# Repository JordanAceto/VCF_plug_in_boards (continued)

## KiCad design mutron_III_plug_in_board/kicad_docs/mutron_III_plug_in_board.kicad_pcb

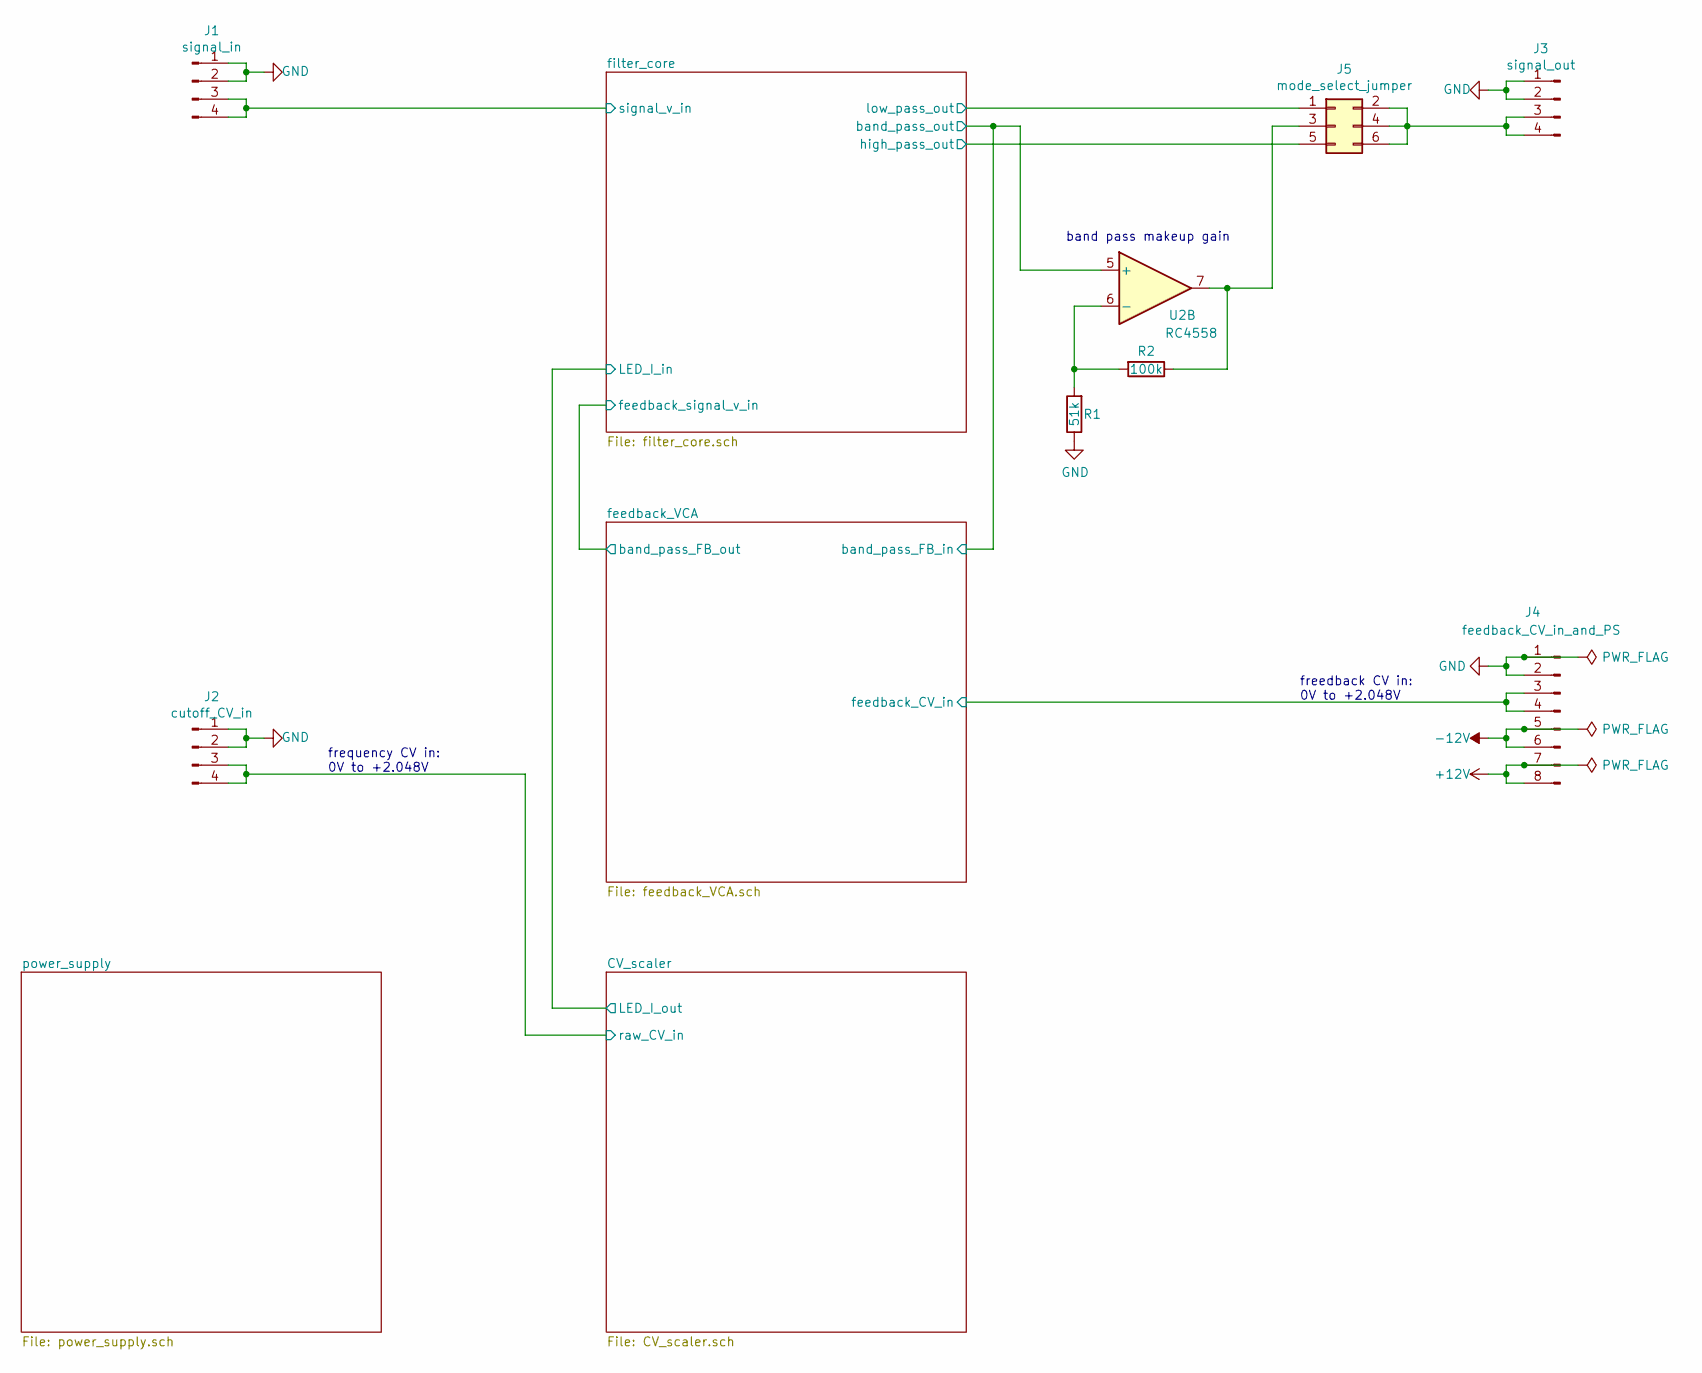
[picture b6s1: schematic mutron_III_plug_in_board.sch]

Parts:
J1: signal_in; PinHeader_1x04_P2.54mm_Vertical
J2: cutoff_CV_in; PinHeader_1x04_P2.54mm_Vertical
J3: signal_out; PinHeader_1x04_P2.54mm_Vertical
J4: feedback_CV_in_and_PS; PinHeader_1x08_P2.54mm_Vertical
J5: mode_select_jumper; PinHeader_2x03_P2.54mm_Vertical
R1: 51k; R_0805_2012Metric_Pad1.15x1.40mm_HandSolder
R2: 100k; R_0805_2012Metric_Pad1.15x1.40mm_HandSolder
U2: RC4558; SOIC-8_3.9x4.9mm_P1.27mm

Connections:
+12V: J4.7, J4.8; also elsewhere on the board
-12V: J4.5, J4.6; also elsewhere on the board
/CV_scaler/raw_CV_in: J2.3, J2.4; also elsewhere on the board
/feedback_VCA/band_pass_FB_in: U2.5 (+); also elsewhere on the board
/feedback_VCA/feedback_CV_in: J4.3, J4.4; also elsewhere on the board
/filter_core/high_pass_out: J5.5; also elsewhere on the board
/filter_core/low_pass_out: J5.1; also elsewhere on the board
/filter_core/signal_v_in: J1.3, J1.4; also elsewhere on the board
GND: J1.1, J1.2, J2.1, J2.2, J3.1, J3.2, J4.1, J4.2, R1.1; also elsewhere on the board
unnamed: J3.3, J3.4, J5.2, J5.4, J5.6
unnamed: J5.3, R2.1, U2.7
unnamed: R1.2, R2.2, U2.6 (-)

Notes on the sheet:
frequency CV in: 0V to +2.048V
freedback CV in: 0V to +2.048V
band pass makeup gain

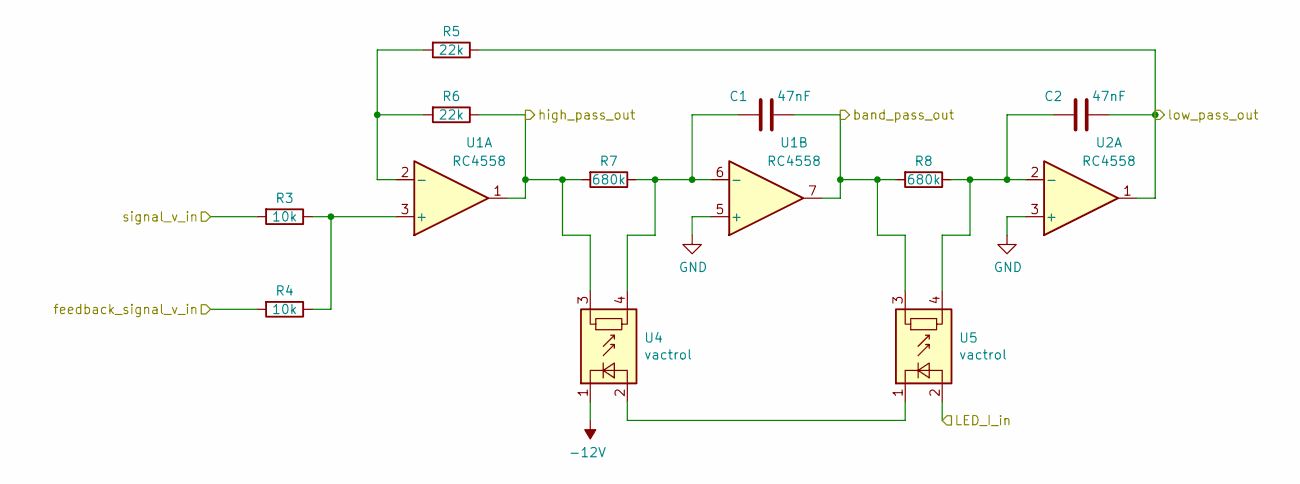
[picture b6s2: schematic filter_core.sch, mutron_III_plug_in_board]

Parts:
C1, C2: 47nF; C_Rect_L7.0mm_W3.5mm_P5.00mm
R3, R4: 10k; R_0805_2012Metric_Pad1.15x1.40mm_HandSolder
R5, R6: 22k; R_0805_2012Metric_Pad1.15x1.40mm_HandSolder
R7, R8: 680k; R_0805_2012Metric_Pad1.15x1.40mm_HandSolder
U1, U2: RC4558; SOIC-8_3.9x4.9mm_P1.27mm
U4, U5: vactrol; vactrol_dual_footprint

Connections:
-12V: U4.1 (-); also elsewhere on the board
/feedback_VCA/band_pass_FB_in: C1.1, R8.2, U1.7, U5.3; also elsewhere on the board
/feedback_VCA/band_pass_FB_out: R4.2; also elsewhere on the board
/filter_core/LED_I_in: U5.2 (+); also elsewhere on the board
/filter_core/high_pass_out: R6.1, R7.2, U1.1, U4.3; also elsewhere on the board
/filter_core/low_pass_out: C2.1, R5.1, U2.1; also elsewhere on the board
/filter_core/signal_v_in: R3.2; also elsewhere on the board
GND: U1.5 (+), U2.3 (+); also elsewhere on the board
unnamed: C1.2, R7.1, U1.6 (-), U4.4
unnamed: C2.2, R8.1, U2.2 (-), U5.4
unnamed: R3.1, R4.1, U1.3 (+)
unnamed: R5.2, R6.2, U1.2 (-)
unnamed: U4.2 (+), U5.1 (-)

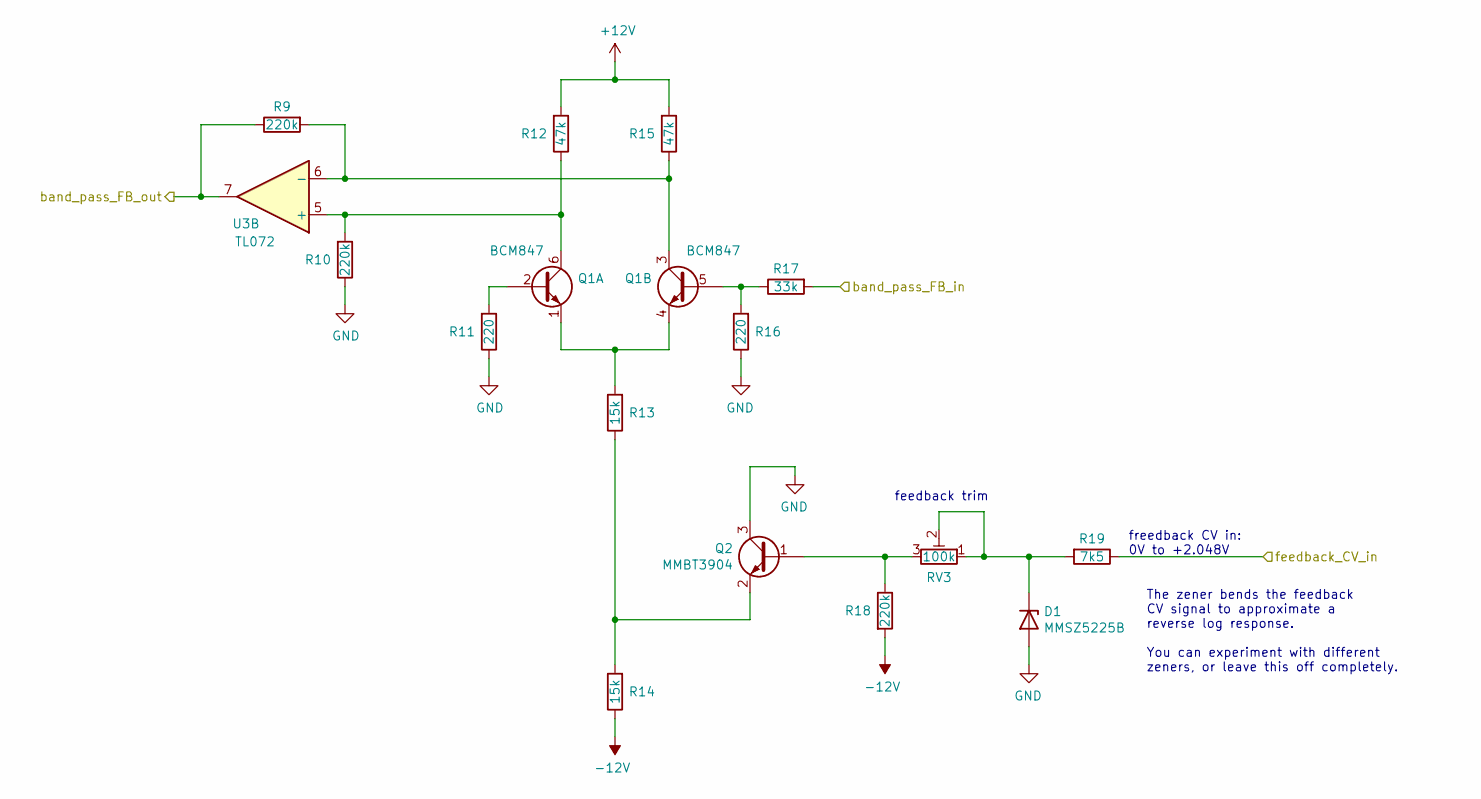
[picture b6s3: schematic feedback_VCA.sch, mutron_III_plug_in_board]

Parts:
D1: MMSZ5225B; D_SOD-123
Q1: BCM847; SOT457
Q2: MMBT3904; SOT-23_Handsoldering
R9, R10, R18: 220k; R_0805_2012Metric_Pad1.15x1.40mm_HandSolder
R11, R16: 220; R_0805_2012Metric_Pad1.15x1.40mm_HandSolder
R12, R15: 47k; R_0805_2012Metric_Pad1.15x1.40mm_HandSolder
R13, R14: 15k; R_0805_2012Metric_Pad1.15x1.40mm_HandSolder
R17: 33k; R_0805_2012Metric_Pad1.15x1.40mm_HandSolder
R19: 7k5; R_0805_2012Metric_Pad1.15x1.40mm_HandSolder
RV3: 100k; Potentiometer_Bourns_3296W_Vertical
U3: TL072; SOIC-8_3.9x4.9mm_P1.27mm

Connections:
+12V: R12.2, R15.2; also elsewhere on the board
-12V: R14.1, R18.2; also elsewhere on the board
/feedback_VCA/band_pass_FB_in: R17.2; also elsewhere on the board
/feedback_VCA/band_pass_FB_out: R9.1, U3.7; also elsewhere on the board
/feedback_VCA/feedback_CV_in: R19.1; also elsewhere on the board
GND: D1.2 (A), Q2.3 (C), R10.1, R11.1, R16.1; also elsewhere on the board
unnamed: D1.1 (K), R19.2, RV3.1, RV3.2
unnamed: Q1.1 (E), Q1.4 (E), R13.2
unnamed: Q1.2 (B), R11.2
unnamed: Q1.3 (C), R9.2, R15.1, U3.6 (-)
unnamed: Q1.5 (B), R16.2, R17.1
unnamed: Q1.6 (C), R10.2, R12.1, U3.5 (+)
unnamed: Q2.1 (B), R18.1, RV3.3
unnamed: Q2.2 (E), R13.1, R14.2

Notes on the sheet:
freedback CV in: 0V to +2.048V
feedback trim
The zener bends the feedback CV signal to approximate a reverse log response. You can experiment with different zeners, or leave this off completely.

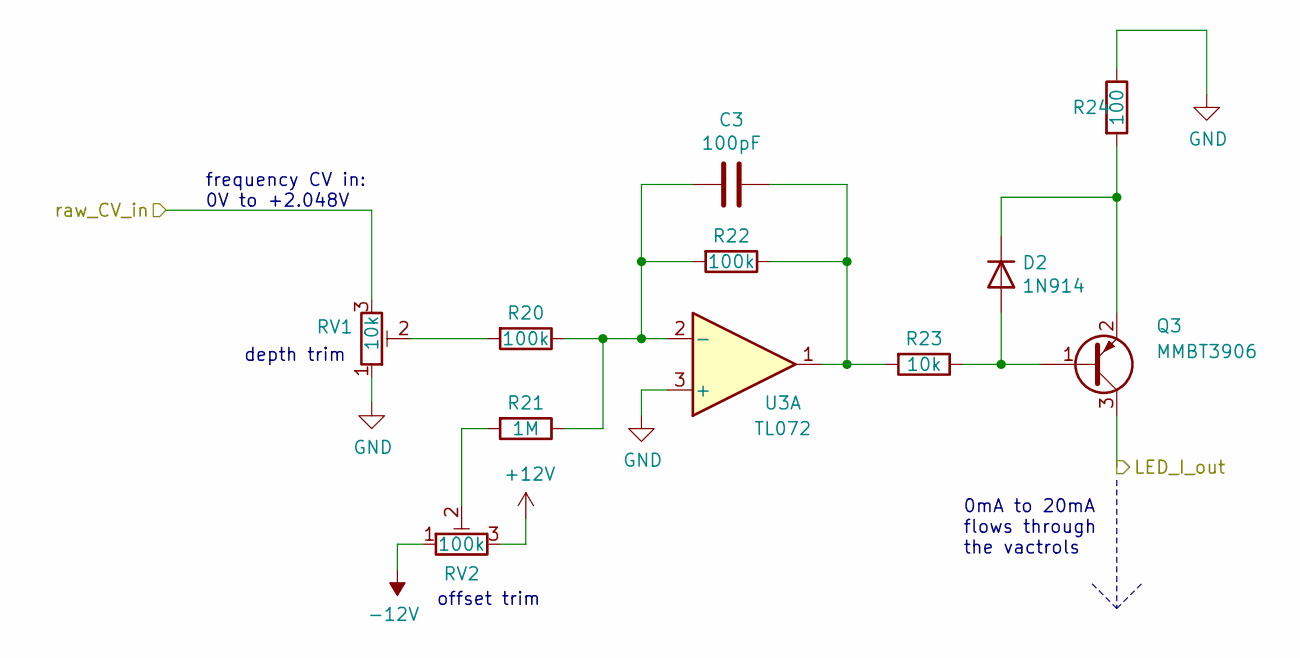
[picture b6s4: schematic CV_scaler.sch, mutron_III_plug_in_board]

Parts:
C3: 100pF; C_0805_2012Metric_Pad1.15x1.40mm_HandSolder
D2: 1N914; D_SOD-123
Q3: MMBT3906; SOT-23_Handsoldering
R20, R22: 100k; R_0805_2012Metric_Pad1.15x1.40mm_HandSolder
R21: 1M; R_0805_2012Metric_Pad1.15x1.40mm_HandSolder
R23: 10k; R_0805_2012Metric_Pad1.15x1.40mm_HandSolder
R24: 100; R_0805_2012Metric_Pad1.15x1.40mm_HandSolder
RV1: 10k; Potentiometer_Bourns_3296W_Vertical
RV2: 100k; Potentiometer_Bourns_3296W_Vertical
U3: TL072; SOIC-8_3.9x4.9mm_P1.27mm

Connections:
+12V: RV2.3; also elsewhere on the board
-12V: RV2.1; also elsewhere on the board
/CV_scaler/raw_CV_in: RV1.3; also elsewhere on the board
/filter_core/LED_I_in: Q3.3 (C); also elsewhere on the board
GND: R24.1, RV1.1, U3.3 (+); also elsewhere on the board
unnamed: C3.1, R22.1, R23.2, U3.1
unnamed: C3.2, R20.1, R21.1, R22.2, U3.2 (-)
unnamed: D2.1 (K), Q3.2 (E), R24.2
unnamed: D2.2 (A), Q3.1 (B), R23.1
unnamed: R20.2, RV1.2
unnamed: R21.2, RV2.2

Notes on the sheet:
0mA to 20mA flows through the vactrols
depth trim
offset trim
frequency CV in: 0V to +2.048V

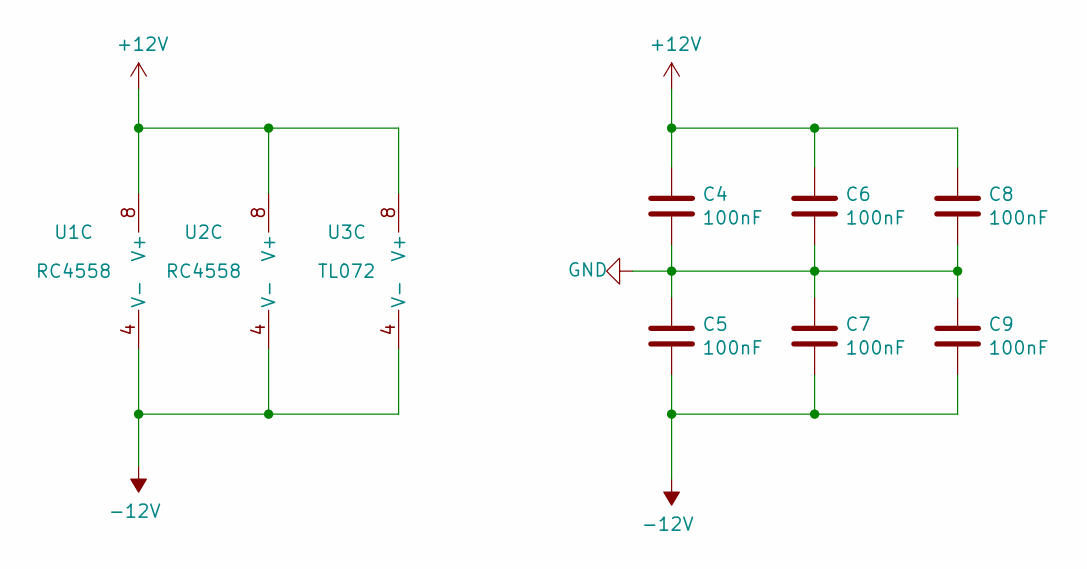
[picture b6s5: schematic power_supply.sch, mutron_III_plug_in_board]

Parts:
C4, C5, C6, C7, C8, C9: 100nF; C_0805_2012Metric_Pad1.15x1.40mm_HandSolder
U1, U2: RC4558; SOIC-8_3.9x4.9mm_P1.27mm
U3: TL072; SOIC-8_3.9x4.9mm_P1.27mm

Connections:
+12V: C4.1, C6.1, C8.1, U1.8 (V+), U2.8 (V+), U3.8 (V+); also elsewhere on the board
-12V: C5.2, C7.2, C9.2, U1.4 (V-), U2.4 (V-), U3.4 (V-); also elsewhere on the board
GND: C4.2, C5.1, C6.2, C7.1, C8.2, C9.1; also elsewhere on the board

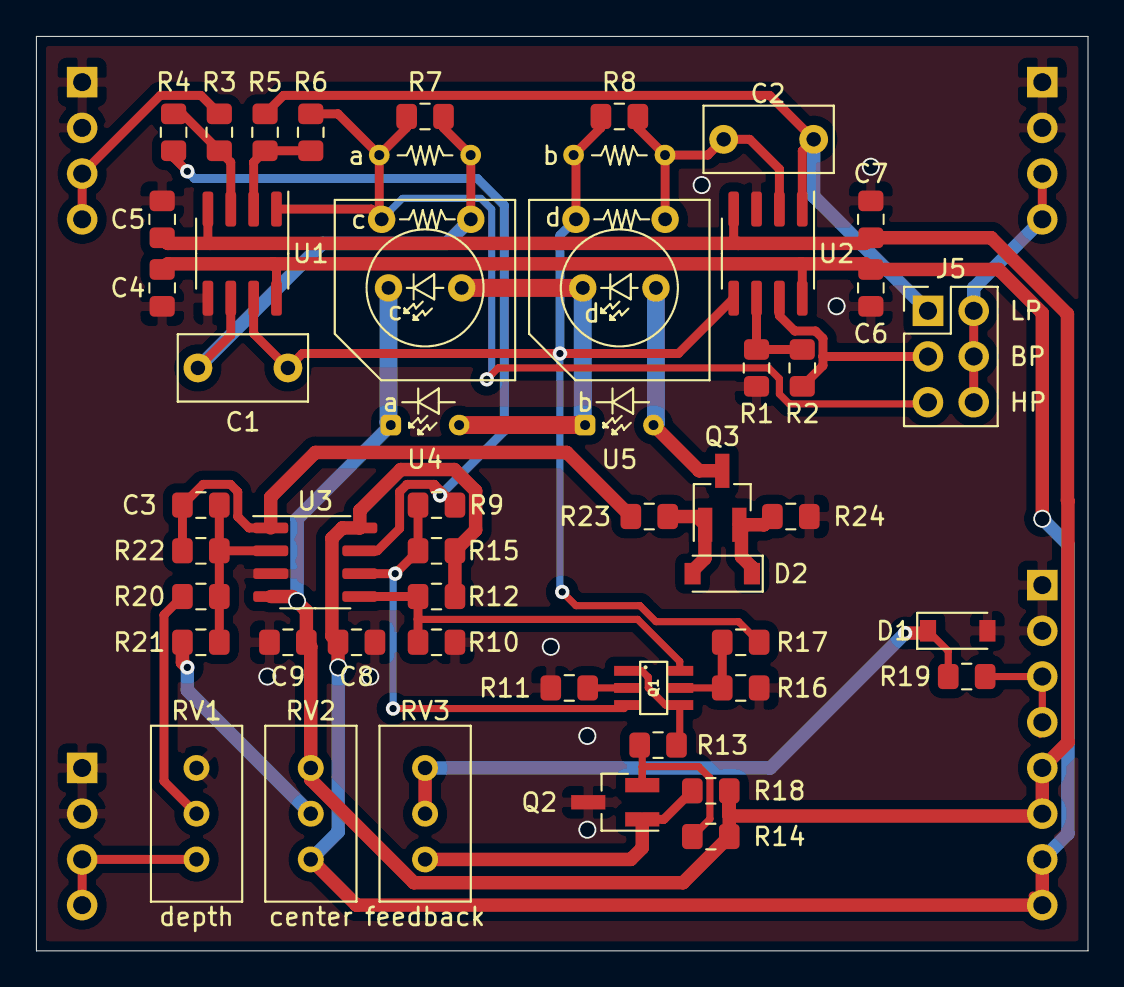
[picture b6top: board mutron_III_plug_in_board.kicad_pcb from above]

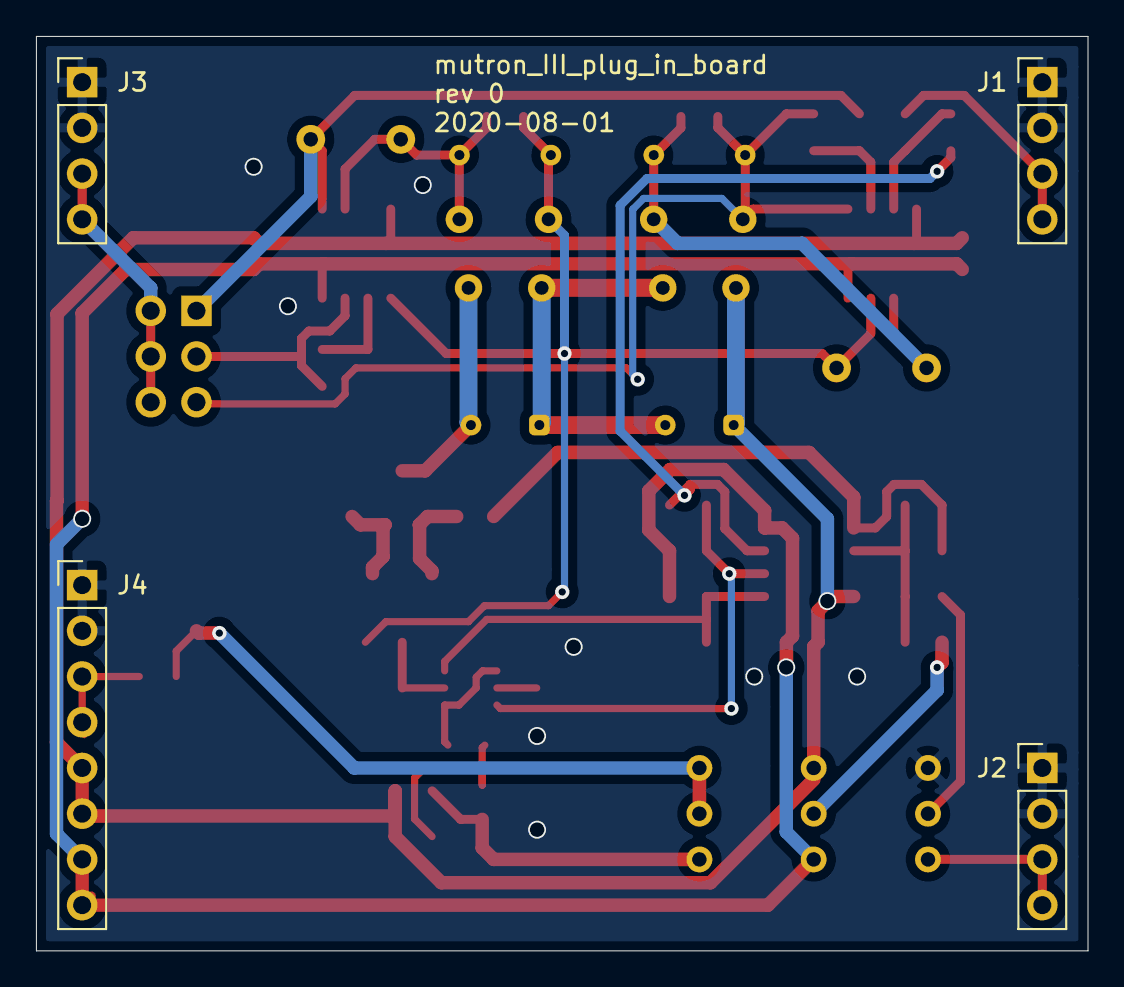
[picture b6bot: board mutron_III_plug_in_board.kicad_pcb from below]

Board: 2 copper layers, 58.4 x 50.8 mm, 51 parts (4 on the bottom side), 33 nets.

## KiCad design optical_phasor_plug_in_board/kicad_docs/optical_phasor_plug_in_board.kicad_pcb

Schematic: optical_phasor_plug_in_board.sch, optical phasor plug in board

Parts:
C1: 33pF; C_0805_2012Metric_Pad1.15x1.40mm_HandSolder
C2, C12, C13, C14, C15, C16, C17: 100nF; C_0805_2012Metric_Pad1.15x1.40mm_HandSolder
C3: 3n3; C_0805_2012Metric_Pad1.15x1.40mm_HandSolder
C4, C21: 1nF; C_0805_2012Metric_Pad1.15x1.40mm_HandSolder
C5, C6, C7, C9, C10, C11: 6n8; C_0805_2012Metric_Pad1.15x1.40mm_HandSolder
C8: 470nF; C_0805_2012Metric_Pad1.15x1.40mm_HandSolder
C20: 470pF; C_0805_2012Metric_Pad1.15x1.40mm_HandSolder
C22: 220nF; C_0805_2012Metric_Pad1.15x1.40mm_HandSolder
D1: 1N914; D_SOD-123
D2: green_diffused; LED_D5.0mm
D8: 1N5225B; D_SOD-123
J1, J2, J3: Conn_01x04_Male; PinHeader_1x04_P2.54mm_Vertical
J4: Conn_01x08_Male; PinHeader_1x08_P2.54mm_Vertical
Q1, Q5: MMBT3906; SOT-23_Handsoldering
Q2: BCM847DS135; SOT457
Q3, Q4: MMBT3904; SOT-23_Handsoldering
R1: 3k9; R_0805_2012Metric_Pad1.15x1.40mm_HandSolder
R2: 390k; R_0805_2012Metric_Pad1.15x1.40mm_HandSolder
R3, R6, R7, R9, R16, R19, R20, R23, R24, R30, R32, R38, R40, R44, R46, R47, R48: 4k7; R_0805_2012Metric_Pad1.15x1.40mm_HandSolder
R4: 8k2; R_0805_2012Metric_Pad1.15x1.40mm_HandSolder
R5, R8, R18, R22, R25, R27, R28, R36, R43: 220k; R_0805_2012Metric_Pad1.15x1.40mm_HandSolder
R10: 68k; R_0805_2012Metric_Pad1.15x1.40mm_HandSolder
R11: 1M; R_0805_2012Metric_Pad1.15x1.40mm_HandSolder
R12: 10k; R_0805_2012Metric_Pad1.15x1.40mm_HandSolder
R13: 100R; R_0805_2012Metric_Pad1.15x1.40mm_HandSolder
R14, R17, R21, R26, R34, R41: LDR; R_LDR_5.0x4.1mm_P3mm_Vertical
R15, R37: 100k; R_0805_2012Metric_Pad1.15x1.40mm_HandSolder
R29, R35: 220R; R_0805_2012Metric_Pad1.15x1.40mm_HandSolder
R31, R33: 47k; R_0805_2012Metric_Pad1.15x1.40mm_HandSolder
R39: 680k; R_0805_2012Metric_Pad1.15x1.40mm_HandSolder
R42: 7k5; R_0805_2012Metric_Pad1.15x1.40mm_HandSolder
R45: 12k; R_0805_2012Metric_Pad1.15x1.40mm_HandSolder
RV1: 10k; Potentiometer_Bourns_3269W_Vertical
RV2: 100k; Potentiometer_Bourns_3269W_Vertical
RV3: 50k; Potentiometer_Bourns_3269W_Vertical
U1, U2, U3, U4, U5: RC4558; SOIC-8_3.9x4.9mm_P1.27mm
U6: TL072; SOIC-8_3.9x4.9mm_P1.27mm

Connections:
+12V: C12.1, C14.1, C16.1, J4.7, J4.8, R31.2, R33.2, R39.1, RV2.3, U1.8 (V+), U2.8 (V+), U3.8 (V+), U4.8 (V+), U5.8 (V+), U6.8 (V+)
-12V: C13.1, C15.1, C17.1, D2.1 (K), J4.5, J4.6, Q3.2 (E), Q4.2 (E), RV2.1, U1.4 (V-), U2.4 (V-), U3.4 (V-), U4.4 (V-), U5.4 (V-), U6.4 (V-)
GND: C1.2, C3.2, C12.2, C13.2, C14.2, C15.2, C16.2, C17.2, C20.1, D8.2 (A), J1.1, J1.2, J2.1, J2.2, J3.1, J3.2, J4.1, J4.2, Q5.1 (B), R5.1, R8.1, R13.2, R14.2, R17.2, R18.1, R21.2, R22.1, R26.2, R27.1, R28.1, R29.1, R34.2, R35.1, R36.1, R41.2, R43.1, RV1.1, U5.3 (+), U6.3 (+)
unnamed: C1.1, R1.2, U1.3 (+)
unnamed: C2.1, R2.1, R3.2, R45.2, U1.1
unnamed: C2.2, R2.2, U1.2 (-)
unnamed: C3.1, R4.2, R5.2, U1.5 (+)
unnamed: C4.1, R3.1, R6.2, U1.6 (-)
unnamed: C4.2, C5.2, R6.1, R7.2, U1.7
unnamed: C5.1, R8.2, R14.1, U2.5 (+)
unnamed: C6.1, R17.1, R18.2, U2.3 (+)
unnamed: C6.2, R9.1, R16.2, U2.7
unnamed: C7.1, R21.1, R22.2, U3.3 (+)
unnamed: C7.2, R19.1, R20.2, U2.1
unnamed: C8.1, R4.1
unnamed: C8.2, R25.1, U6.7
unnamed: C9.1, R26.1, R28.2, U3.5 (+)
unnamed: C9.2, R23.1, R24.2, U3.1
unnamed: C10.1, R34.1, R36.2, U4.5 (+)
unnamed: C10.2, R30.1, R32.2, U3.7
unnamed: C11.1, R41.1, R43.2, U4.3 (+)
unnamed: C11.2, R38.1, R40.2, U4.7
unnamed: C20.2, R45.1, R46.1, U5.5 (+)
unnamed: C21.1, C22.2, R48.1, U5.1
unnamed: C21.2, R47.1, R48.2, U5.2 (-)
unnamed: C22.1, R46.2
unnamed: D1.1 (K), Q1.2 (E), R13.1
unnamed: D1.2 (A), Q1.1 (B), R12.1
unnamed: D2.2 (A), Q1.3 (C)
unnamed: D8.1 (K), R42.1, RV3.1, RV3.2
unnamed: J1.3, J1.4, RV1.3
unnamed: J2.3, J2.4, R1.1
unnamed: J3.3, J3.4, U5.6 (-), U5.7
unnamed: J4.3, J4.4, R42.2
unnamed: Q2.1 (E), Q2.4 (E), Q3.3 (C)
unnamed: Q2.2 (B), R29.2
unnamed: Q2.3 (C), R25.2, R33.1, U6.6 (-)
unnamed: Q2.5 (B), R35.2, R37.1
unnamed: Q2.6 (C), R27.2, R31.1, U6.5 (+)
unnamed: Q3.1 (B), Q4.1 (B), Q4.3 (C), Q5.3 (C)
unnamed: Q5.2 (E), R39.2, RV3.3
unnamed: R7.1, R9.2, U2.6 (-)
unnamed: R10.1, R11.1, R15.2, U6.2 (-)
unnamed: R10.2, RV1.2
unnamed: R11.2, RV2.2
unnamed: R12.2, R15.1, U6.1
unnamed: R16.1, R19.2, U2.2 (-)
unnamed: R20.1, R23.2, U3.2 (-)
unnamed: R24.1, R30.2, U3.6 (-)
unnamed: R32.1, R38.2, U4.6 (-)
unnamed: R37.2, R44.1, R47.2, U4.1
unnamed: R40.1, R44.2, U4.2 (-)

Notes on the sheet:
offset trim
depth trim
zener D8 bends feedback CV to approximate reverse log response
signal in
frequency CV in: 0V to 2.048V
signal out
feedback CV: in 0V to 2.048V
D2 shines on 6 LDRs arranged in a circle.
0mA to 20mA
Attribution: 6 stage all pass filter with feedback is a near copy of the famous Mutron Biphase circuit. Feedback VCA is a near copy of VCA-3 from Rene Schmitz www.schmitzbits.de/vca.html#
feedback trim

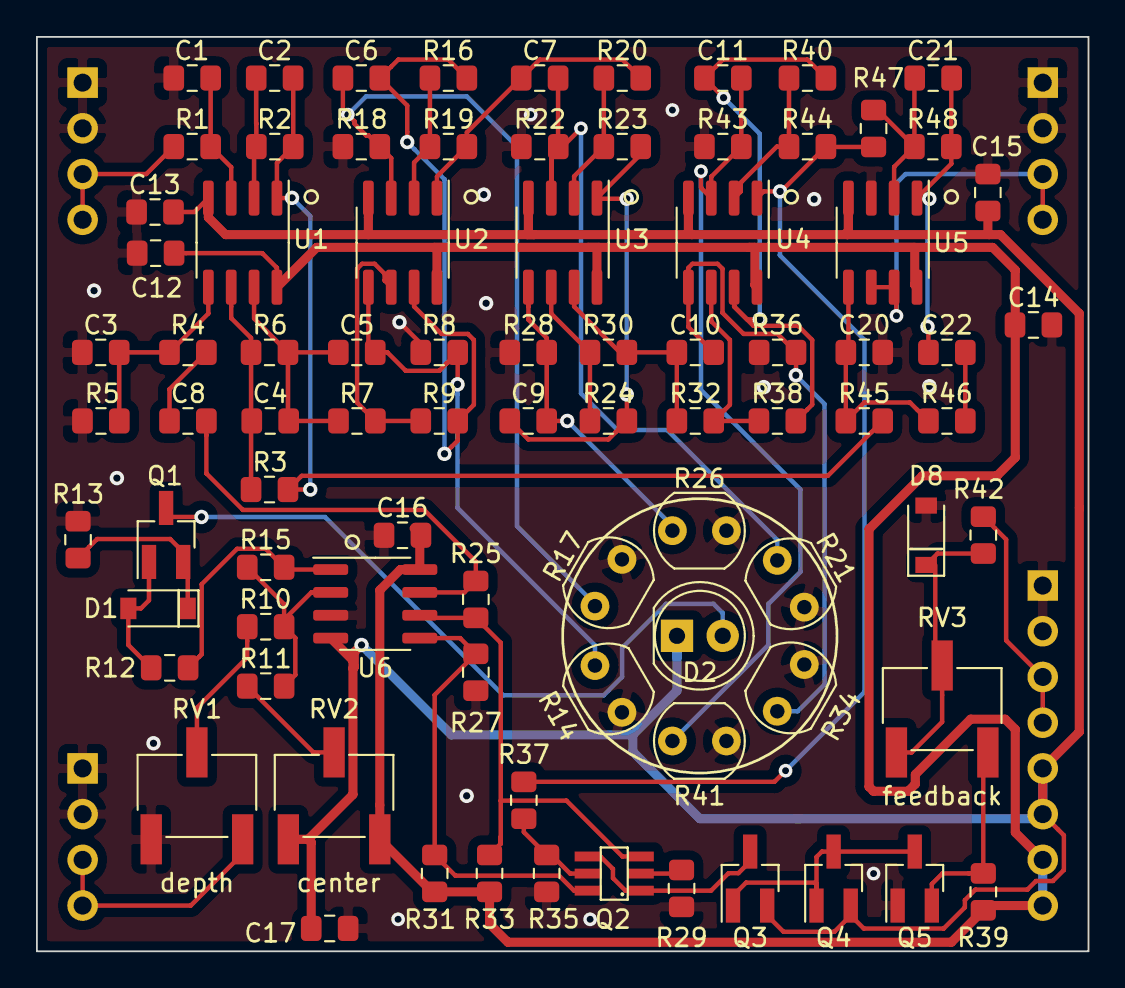
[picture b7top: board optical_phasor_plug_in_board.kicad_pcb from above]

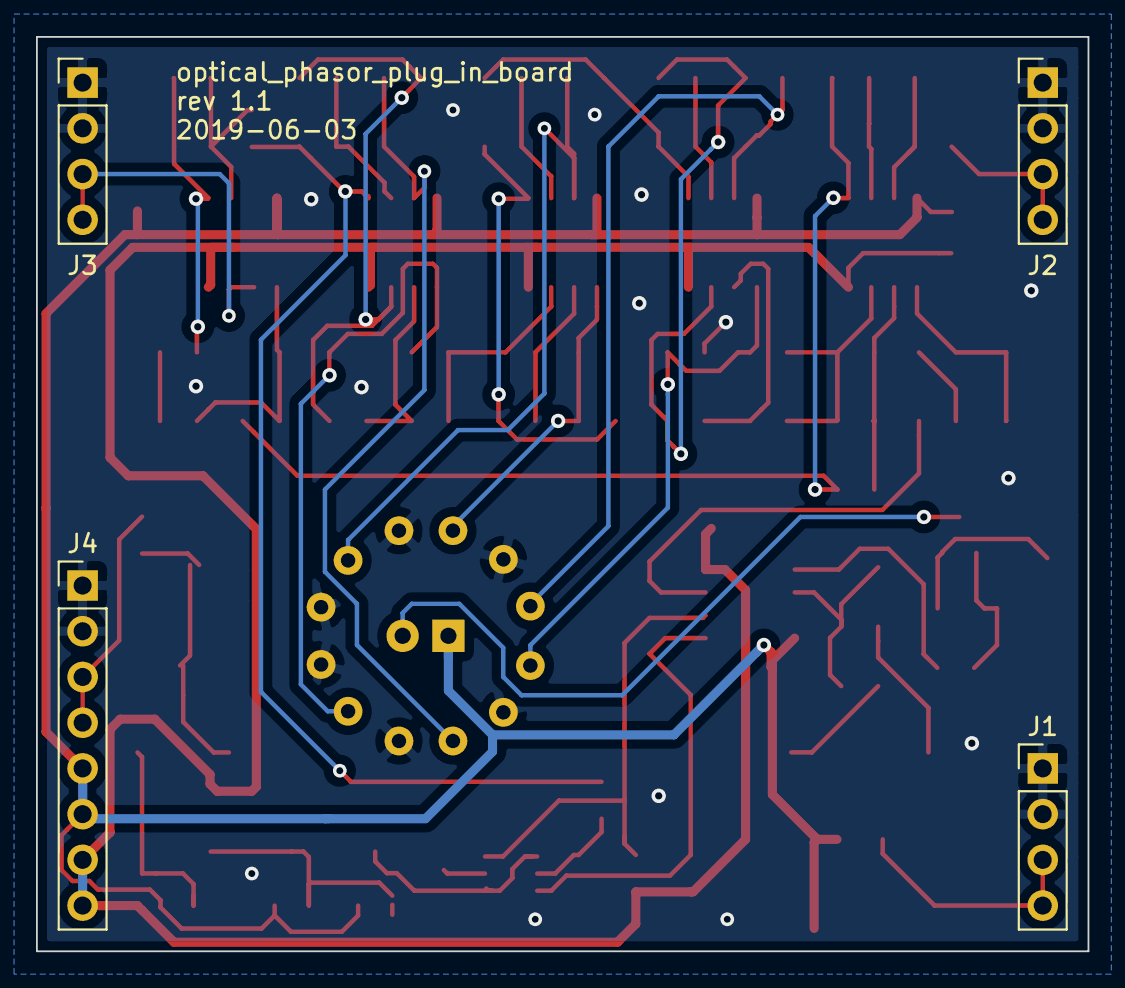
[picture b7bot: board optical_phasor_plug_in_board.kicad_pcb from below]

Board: 2 copper layers, 58.4 x 50.8 mm, 89 parts (4 on the bottom side), 52 nets.

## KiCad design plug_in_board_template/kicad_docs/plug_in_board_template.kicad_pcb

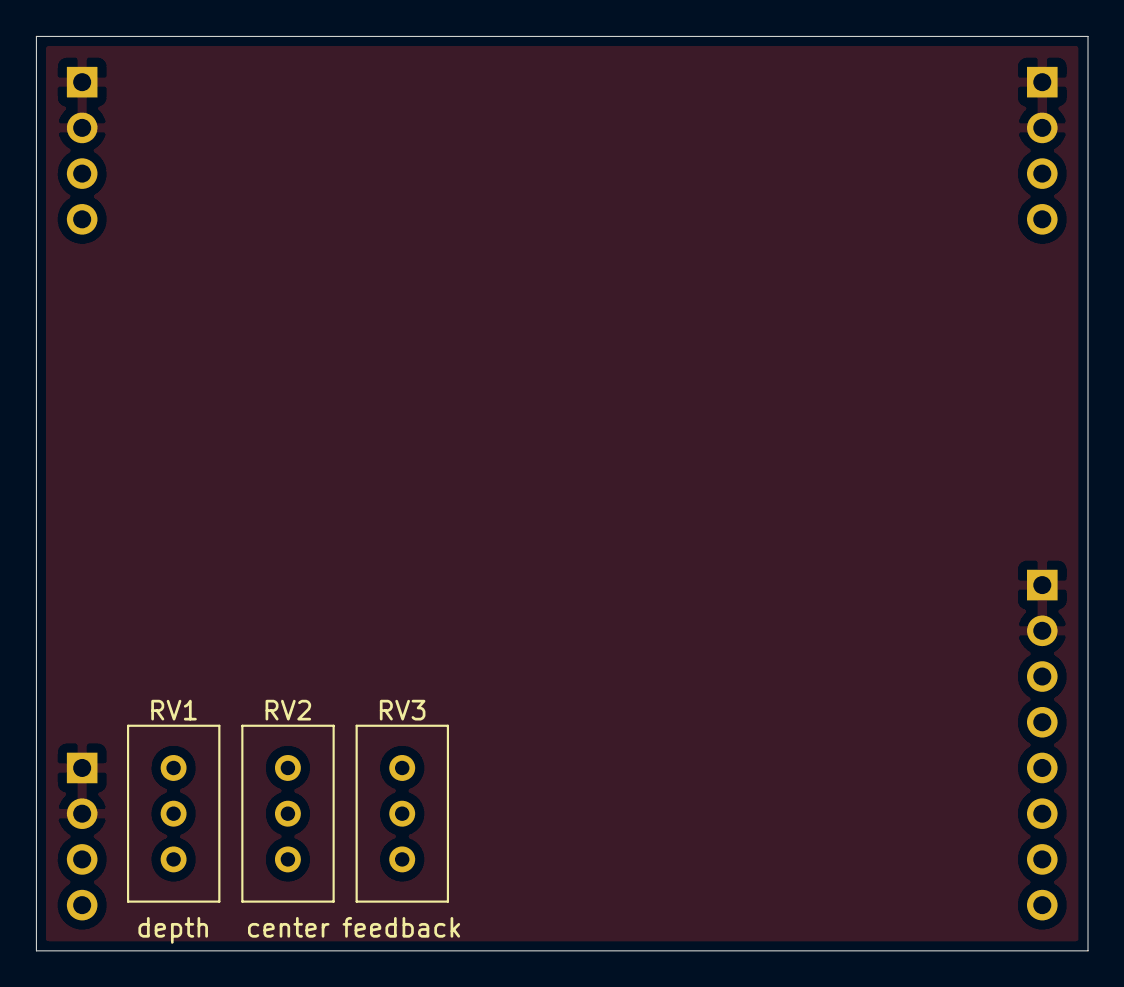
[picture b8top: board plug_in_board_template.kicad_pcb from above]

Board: 2 copper layers, 58.4 x 50.8 mm, 7 parts (4 on the bottom side), 7 nets.

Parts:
J1: signal_input; PinHeader_1x04_P2.54mm_Vertical
J2: cutoff_CV_input; PinHeader_1x04_P2.54mm_Vertical
J3: signal_output; PinHeader_1x04_P2.54mm_Vertical
J4: feedback_CV_and_PS; PinHeader_1x08_P2.54mm_Vertical
RV1, RV2, RV3: ?; Potentiometer_Bourns_3296W_Vertical

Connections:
+12V: J4.7, J4.8
-12V: J4.5, J4.6
GND: J1.1, J1.2, J2.1, J2.2, J3.1, J3.2, J4.1, J4.2
unnamed: J1.3, J1.4
unnamed: J2.3, J2.4
unnamed: J3.3, J3.4
unnamed: J4.3, J4.4
